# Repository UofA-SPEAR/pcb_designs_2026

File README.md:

# pcb_designs_2026
Repository for SPEAR 2026 PCB designs. KiCad is used as the PCB design software.
## Setup Instructions
Before opening any KiCad projects in this repository, the SPEAR_PCB_2026_DIR environment variable must be set as follows:

1. In the top toolbar, click "Preferences" then click "Configure Paths..." in the dropdown menu that appears as shown in figure 1.

**Figure 1**: Configuring KiCad file paths.

2. In the window that shows up, press the "+" button at the bottom left as shown in figure 2. This adds a new empty environment variable at the bottom of the environment variables list.

**Figure 2**: Adding a new environment variable.

3. Edit the name of the environment variable to be "SPEAR_PCB_2026_DIR" and edit the path to be the pcb_designs_2026 git repository. Setting the path can be done by clicking the folder button to the right of the path entry box with the entry box selected. The end result must look like figure 3.

**Figure 3**: Creating the SPEAR_PCB_2026_DIR environment variable.

4. Next, press "OK" to finalize the changes. Now your KiCad is ready to open projects in the repository.

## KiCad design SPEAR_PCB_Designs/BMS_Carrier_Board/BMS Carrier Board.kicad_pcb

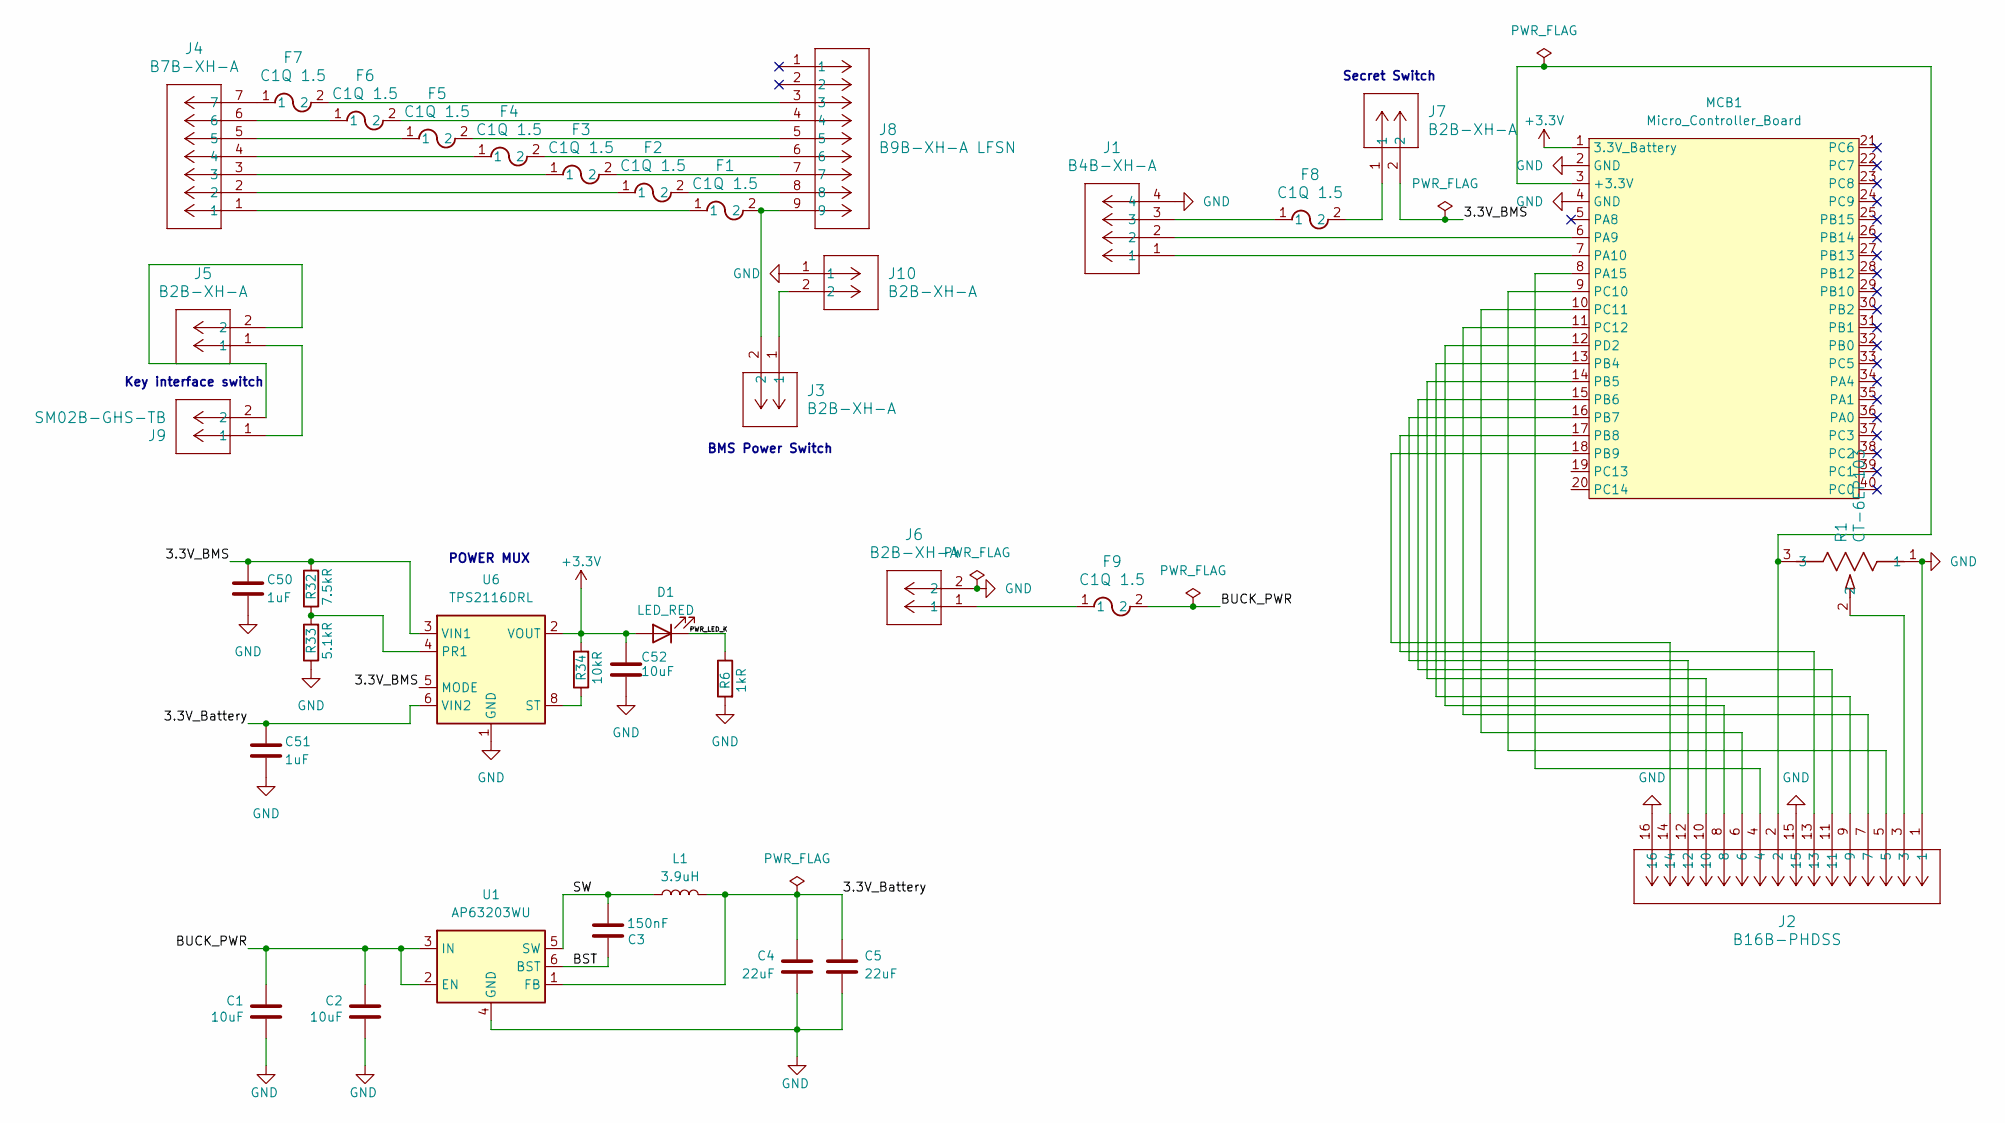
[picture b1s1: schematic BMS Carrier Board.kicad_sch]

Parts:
C1, C2: 10uF; CAPC3225X270N; DigiKey_Part_Number 490-14536-1-ND
C3: 150nF; CAP_CC1206_YAG; DigiKey_Part_Number 13-CC1206KRX7R8BB154CT-ND
C4, C5: 22uF; CAP_C3225X7R1C226M250AC; DigiKey_Part_Number 445-3955-1-ND
C50, C51: 1uF; C_0402_1005Metric; DigiKey_Part_Number 1276-1067-1-ND
C52: 10uF; C_0603_1608Metric; DigiKey_Part_Number 1276-1192-1-ND
D1: LED_RED; LED_0603_1608Metric; DigiKey_Part_Number 732-12015-1-ND
F1, F2, F3, F4, F5, F6, F7, F8, F9: C1Q 1.5; C1_BEL; DigiKey_Part_Number 5923-C1Q1.5CT-ND
J1: B4B-XH-A; CONN_B4B-XH-A_JST; DigiKey_Part_Number 455-B4B-XH-A-ND
J2: B16B-PHDSS; CONN16_B16B-PHDSS_JST
J3, J5, J6, J7: B2B-XH-A; CONN_B2B-XH-A_JST; DigiKey_Part_Number 455-B2B-XH-A-ND
J4: B7B-XH-A; CONN_B7B-XH-A_JST; DigiKey_Part_Number 455-B7B-XH-A-ND
J8: B9B-XH-A LFSN; CONN_B9B-XH-A_JST; DigiKey_Part_Number 455-B9B-XH-A-ND
J9: SM02B-GHS-TB; CONN_SM02B-GHS_JST; DigiKey_Part_Number 455-1564-1-ND
J10: B2B-XH-A; CONN_B2B-XH-A_JST
L1: 3.9uH; L_Wurth_WE-LHMI-1040_L1; DigiKey_Part_Number 732-74437368039CT-ND
MCB1: Micro_Controller_Board
R1: CT-6EP103; POT_CT-6EP103_NDC
R6: 1kR; R_0402_1005Metric; DigiKey_Part_Number 311-1.0KJRCT-ND
R32: 7.5kR; R_0402_1005Metric; DigiKey_Part_Number 311-7.50KLRCT-ND
R33: 5.1kR; R_0402_1005Metric; DigiKey_Part_Number 311-5.10KLRCT-ND
R34: 10kR; R_0402_1005Metric; DigiKey_Part_Number 311-10KJRCT-ND
U1: AP63203WU; TSOT-23-6; DigiKey_Part_Number AP63203WU-7DICT-ND
U6: TPS2116DRL; SOT-583-8; DigiKey_Part_Number 296-TPS2116DRLRCT-ND

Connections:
+3.3V: C52.1, D1.2 (A), MCB1.1 (3.3V_Battery), R34.2, U6.2 (VOUT), U6.7 (VOUT)
/3.3V_BMS: C50.1, J7.2, R32.2, U6.3 (VIN1), U6.5 (MODE)
/3.3V_Battery: C4.1, C5.1, C51.1, L1.2, U1.1 (FB), U6.6 (VIN2)
/BST: C3.2, U1.6 (BST)
/BUCK_PWR: C1.1, C2.1, F9.2, U1.2 (EN), U1.3 (IN)
/PWR_LED_K: D1.1 (K), R6.1
/SW: C3.1, L1.1, U1.5 (SW)
GND: C1.2, C2.2, C4.2, C5.2, C50.2, C51.2, C52.2, J1.4, J2.1, J2.15, J2.16, J6.2, J10.1, MCB1.2 (GND), MCB1.4 (GND), R1.1, R6.2, R33.1, U1.4 (GND), U6.1 (GND)
unnamed: F1.1, J4.1
unnamed: F1.2, J3.2, J8.9
unnamed: F2.1, J4.2
unnamed: F2.2, J8.8
unnamed: F3.1, J4.3
unnamed: F3.2, J8.7
unnamed: F4.1, J4.4
unnamed: F4.2, J8.6
unnamed: F5.1, J4.5
unnamed: F5.2, J8.5
unnamed: F6.1, J4.6
unnamed: F6.2, J8.4
unnamed: F7.1, J4.7
unnamed: F7.2, J8.3
unnamed: F8.1, J1.3
unnamed: F8.2, J7.1
unnamed: F9.1, J6.1
unnamed: J2.3, R1.2
unnamed: J5.1, J9.1
unnamed: J5.2, J9.2
unnamed: J3.1, J10.2
unnamed: J2.2, MCB1.3 (+3.3V), R1.3
unnamed: J1.2, MCB1.6 (PA9)
unnamed: J1.1, MCB1.7 (PA10)
unnamed: J2.4, MCB1.8 (PA15)
unnamed: J2.9, MCB1.13 (PB4)
unnamed: J2.10, MCB1.14 (PB5)
unnamed: J2.11, MCB1.15 (PB6)
unnamed: J2.12, MCB1.16 (PB7)
unnamed: J2.13, MCB1.17 (PB8)
unnamed: J2.14, MCB1.18 (PB9)
unnamed: J2.5, MCB1.9 (PC10)
unnamed: J2.6, MCB1.10 (PC11)
unnamed: J2.7, MCB1.11 (PC12)
unnamed: J2.8, MCB1.12 (PD2)
unnamed: R32.1, R33.2, U6.4 (PR1)
unnamed: R34.1, U6.8 (ST)

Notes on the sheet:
Key interface switch
POWER MUX
BMS Power Switch
Secret Switch

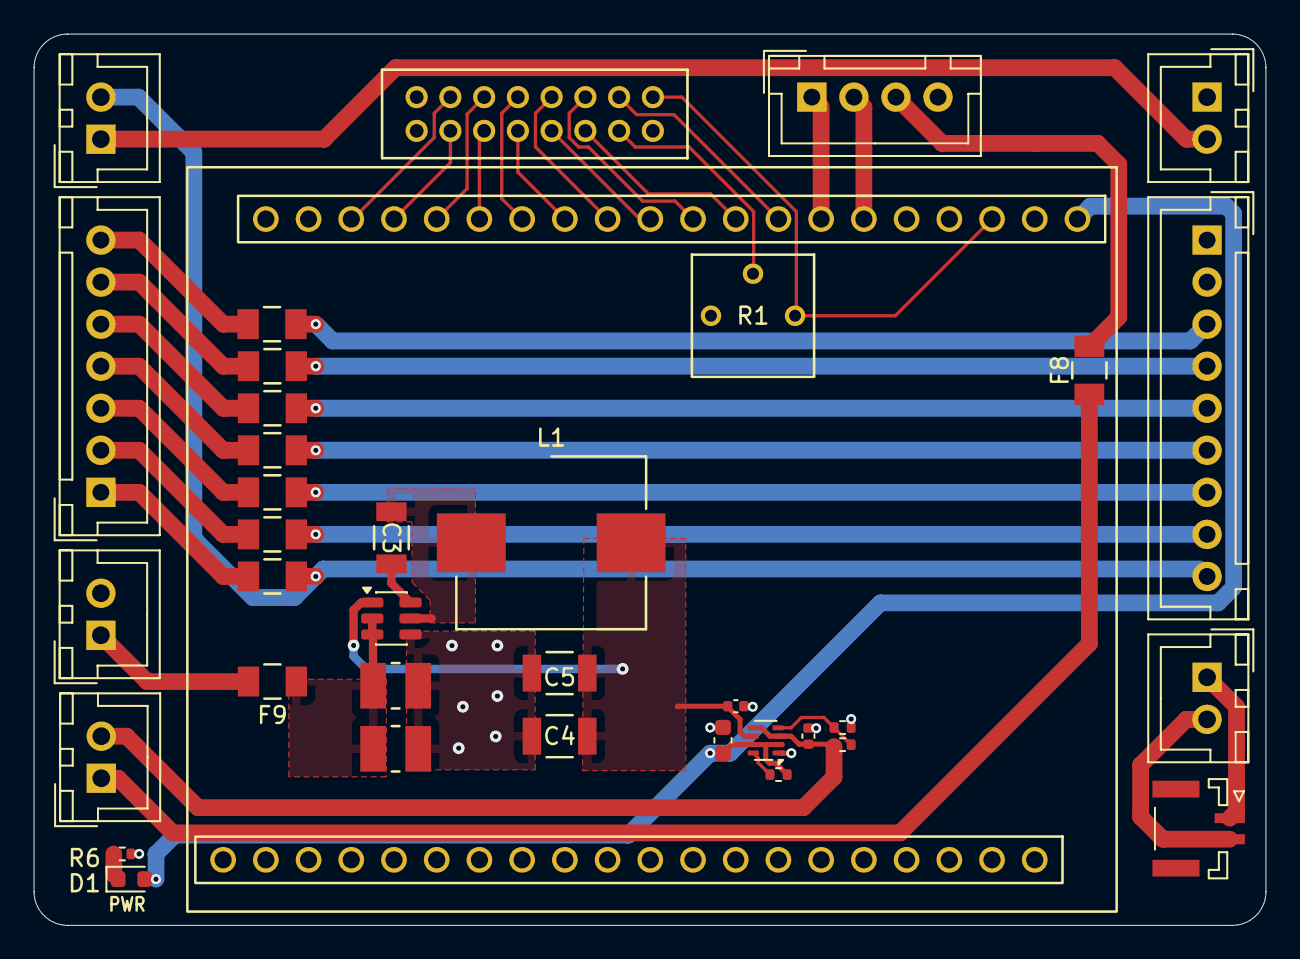
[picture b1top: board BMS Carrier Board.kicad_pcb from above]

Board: 2 copper layers, 73.2 x 53.0 mm, 37 parts (0 on the bottom side), 45 nets.

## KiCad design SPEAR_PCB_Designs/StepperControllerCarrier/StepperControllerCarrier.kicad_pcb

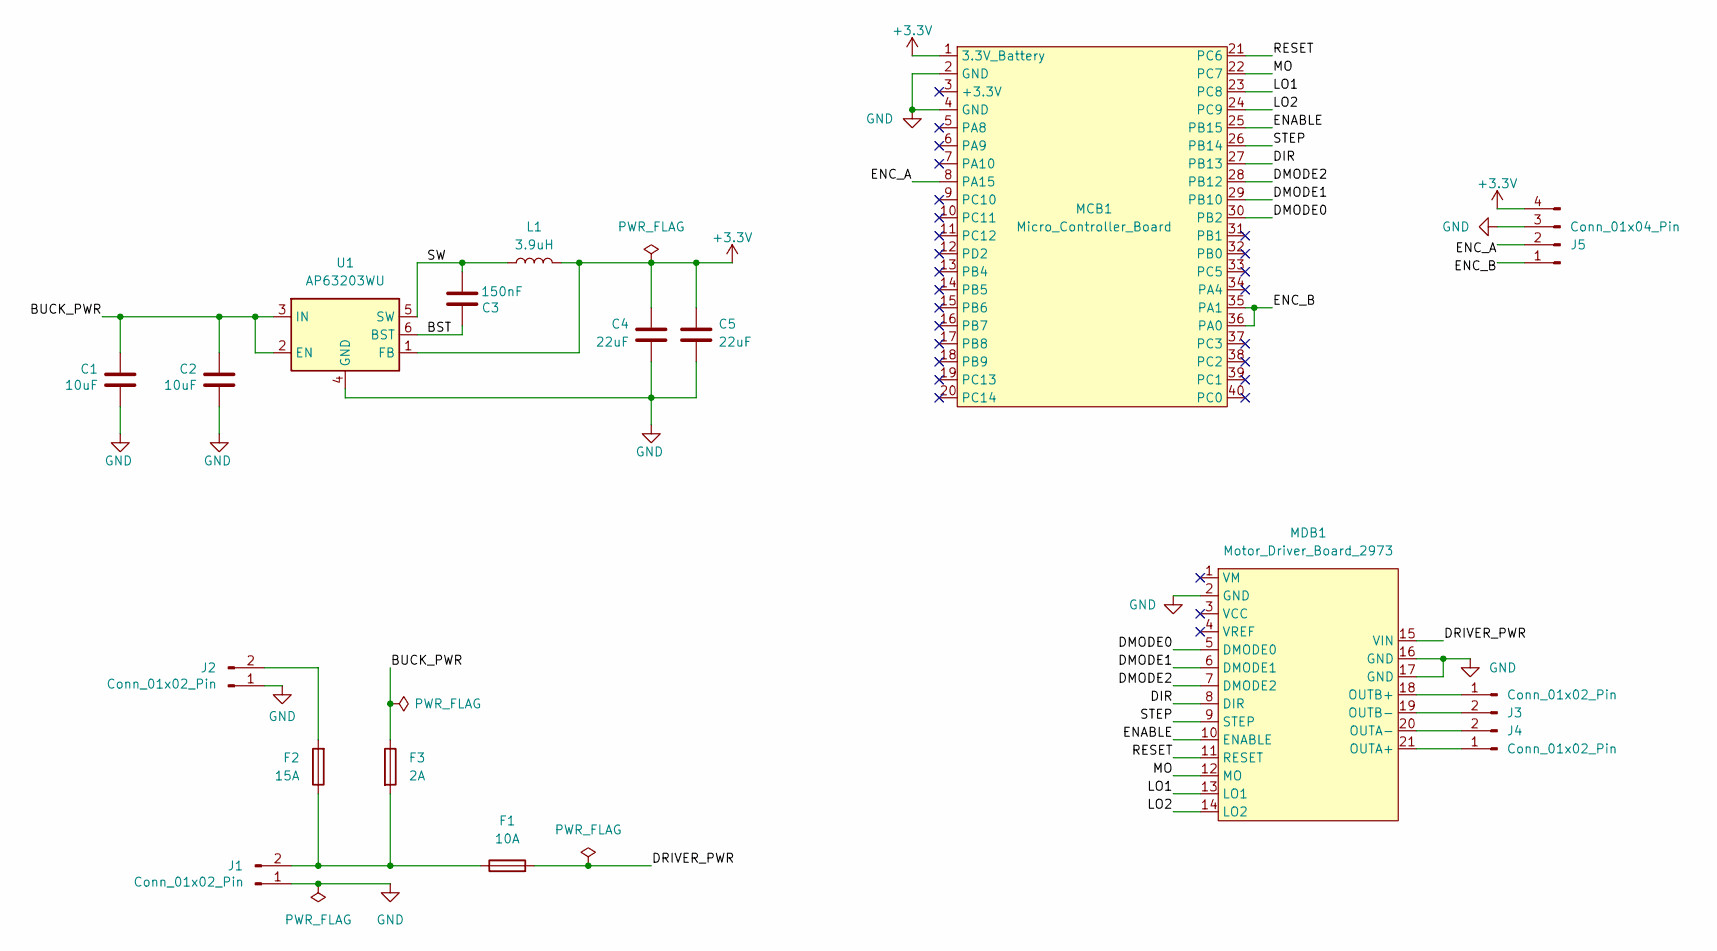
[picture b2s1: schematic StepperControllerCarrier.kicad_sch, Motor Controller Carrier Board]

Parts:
C1, C2: 10uF; CAPC3225X270N; DigiKey_Part_Number 490-14536-1-ND
C3: 150nF; CAP_CC1206_YAG; DigiKey_Part_Number 13-CC1206KRX7R8BB154CT-ND
C4, C5: 22uF; CAP_C3225X7R1C226M250AC; DigiKey_Part_Number 445-3955-1-ND
F1: 10A; FUSE_3557-10; PARTREV D; DigiKey_Part_Number 36-3557-10-ND
F2: 15A; FUSE_3557-15; PARTREV D; DigiKey_Part_Number 36-3557-15-ND
F3: 2A; FUS_LITTELFUSE_392_LTF; DigiKey_Part_Number F5502CT-ND
J1, J2, J3, J4: Conn_01x02_Pin; AMASS_XT30PW-M_1x02_P2.50mm_Horizontal_1
J5: Conn_01x04_Pin; JST_XH_S4B-XH-A-1_1x04_P2.50mm_Horizontal; DigiKey_Part_Number 455-S4B-XH-A-1-ND
L1: 3.9uH; L_Wurth_WE-LHMI-1040_L1; DigiKey_Part_Number 732-74437368039CT-ND
MCB1: Micro_Controller_Board
MDB1: Motor_Driver_Board_2973
U1: AP63203WU; TSOT-23-6; DigiKey_Part_Number AP63203WU-7DICT-ND

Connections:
+3.3V: C4.1, C5.1, J5.4, L1.2, MCB1.1 (3.3V_Battery), U1.1 (FB)
/BST: C3.2, U1.6 (BST)
/BUCK_PWR: C1.1, C2.1, F3.1, U1.2 (EN), U1.3 (IN)
/DIR: MCB1.27 (PB13), MDB1.8 (DIR)
/DMODE0: MCB1.30 (PB2), MDB1.5 (DMODE0)
/DMODE1: MCB1.29 (PB10), MDB1.6 (DMODE1)
/DMODE2: MCB1.28 (PB12), MDB1.7 (DMODE2)
/DRIVER_PWR: F1.2_1, F1.2_2, MDB1.15 (VIN)
/ENABLE: MCB1.25 (PB15), MDB1.10 (ENABLE)
/ENC_A: J5.2, MCB1.8 (PA15)
/ENC_B: J5.1, MCB1.35 (PA1), MCB1.36 (PA0)
/LO1: MCB1.23 (PC8), MDB1.13 (LO1)
/LO2: MCB1.24 (PC9), MDB1.14 (LO2)
/MO: MCB1.22 (PC7), MDB1.12 (MO)
/RESET: MCB1.21 (PC6), MDB1.11 (RESET)
/STEP: MCB1.26 (PB14), MDB1.9 (STEP)
/SW: C3.1, L1.1, U1.5 (SW)
GND: C1.2, C2.2, C4.2, C5.2, J1.1, J2.1, J5.3, MCB1.2 (GND), MCB1.4 (GND), MDB1.2 (GND), MDB1.16 (GND), MDB1.17 (GND), U1.4 (GND)
unnamed: F1.1_1, F1.1_2, F2.1_1, F2.1_2, F3.2, J1.2
unnamed: F2.2_1, F2.2_2, J2.2
unnamed: J3.1, MDB1.18 (OUTB+)
unnamed: J3.2, MDB1.19 (OUTB-)
unnamed: J4.1, MDB1.21 (OUTA+)
unnamed: J4.2, MDB1.20 (OUTA-)

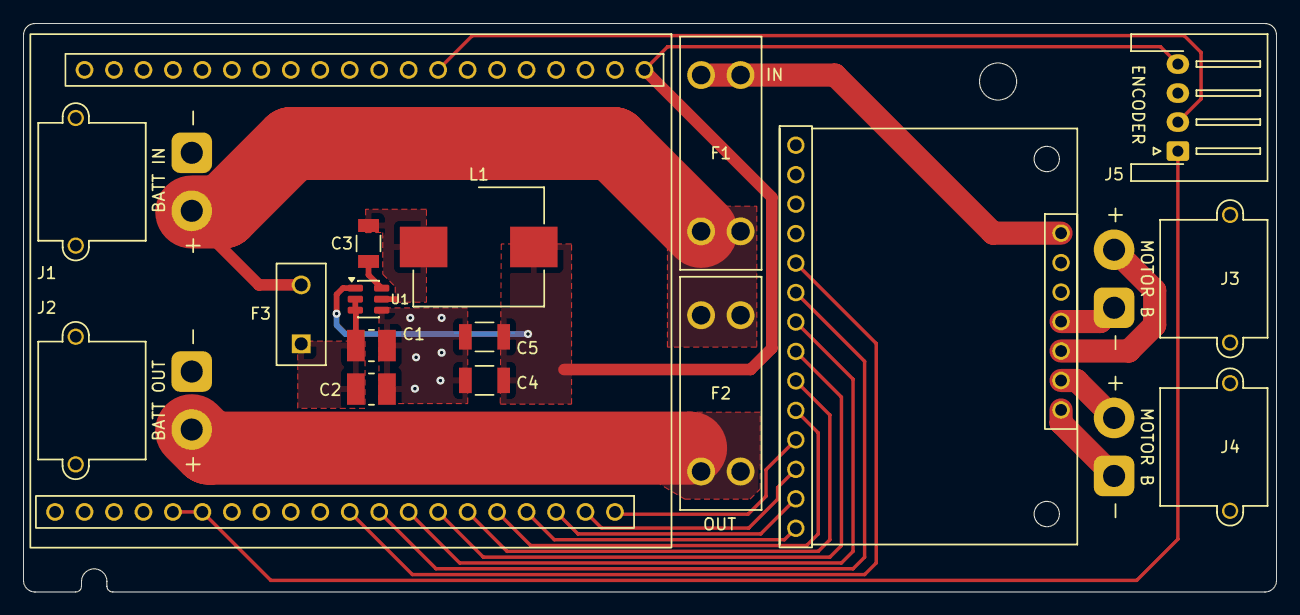
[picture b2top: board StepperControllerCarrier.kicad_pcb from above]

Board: 2 copper layers, 108.0 x 49.0 mm, 17 parts (0 on the bottom side), 24 nets.

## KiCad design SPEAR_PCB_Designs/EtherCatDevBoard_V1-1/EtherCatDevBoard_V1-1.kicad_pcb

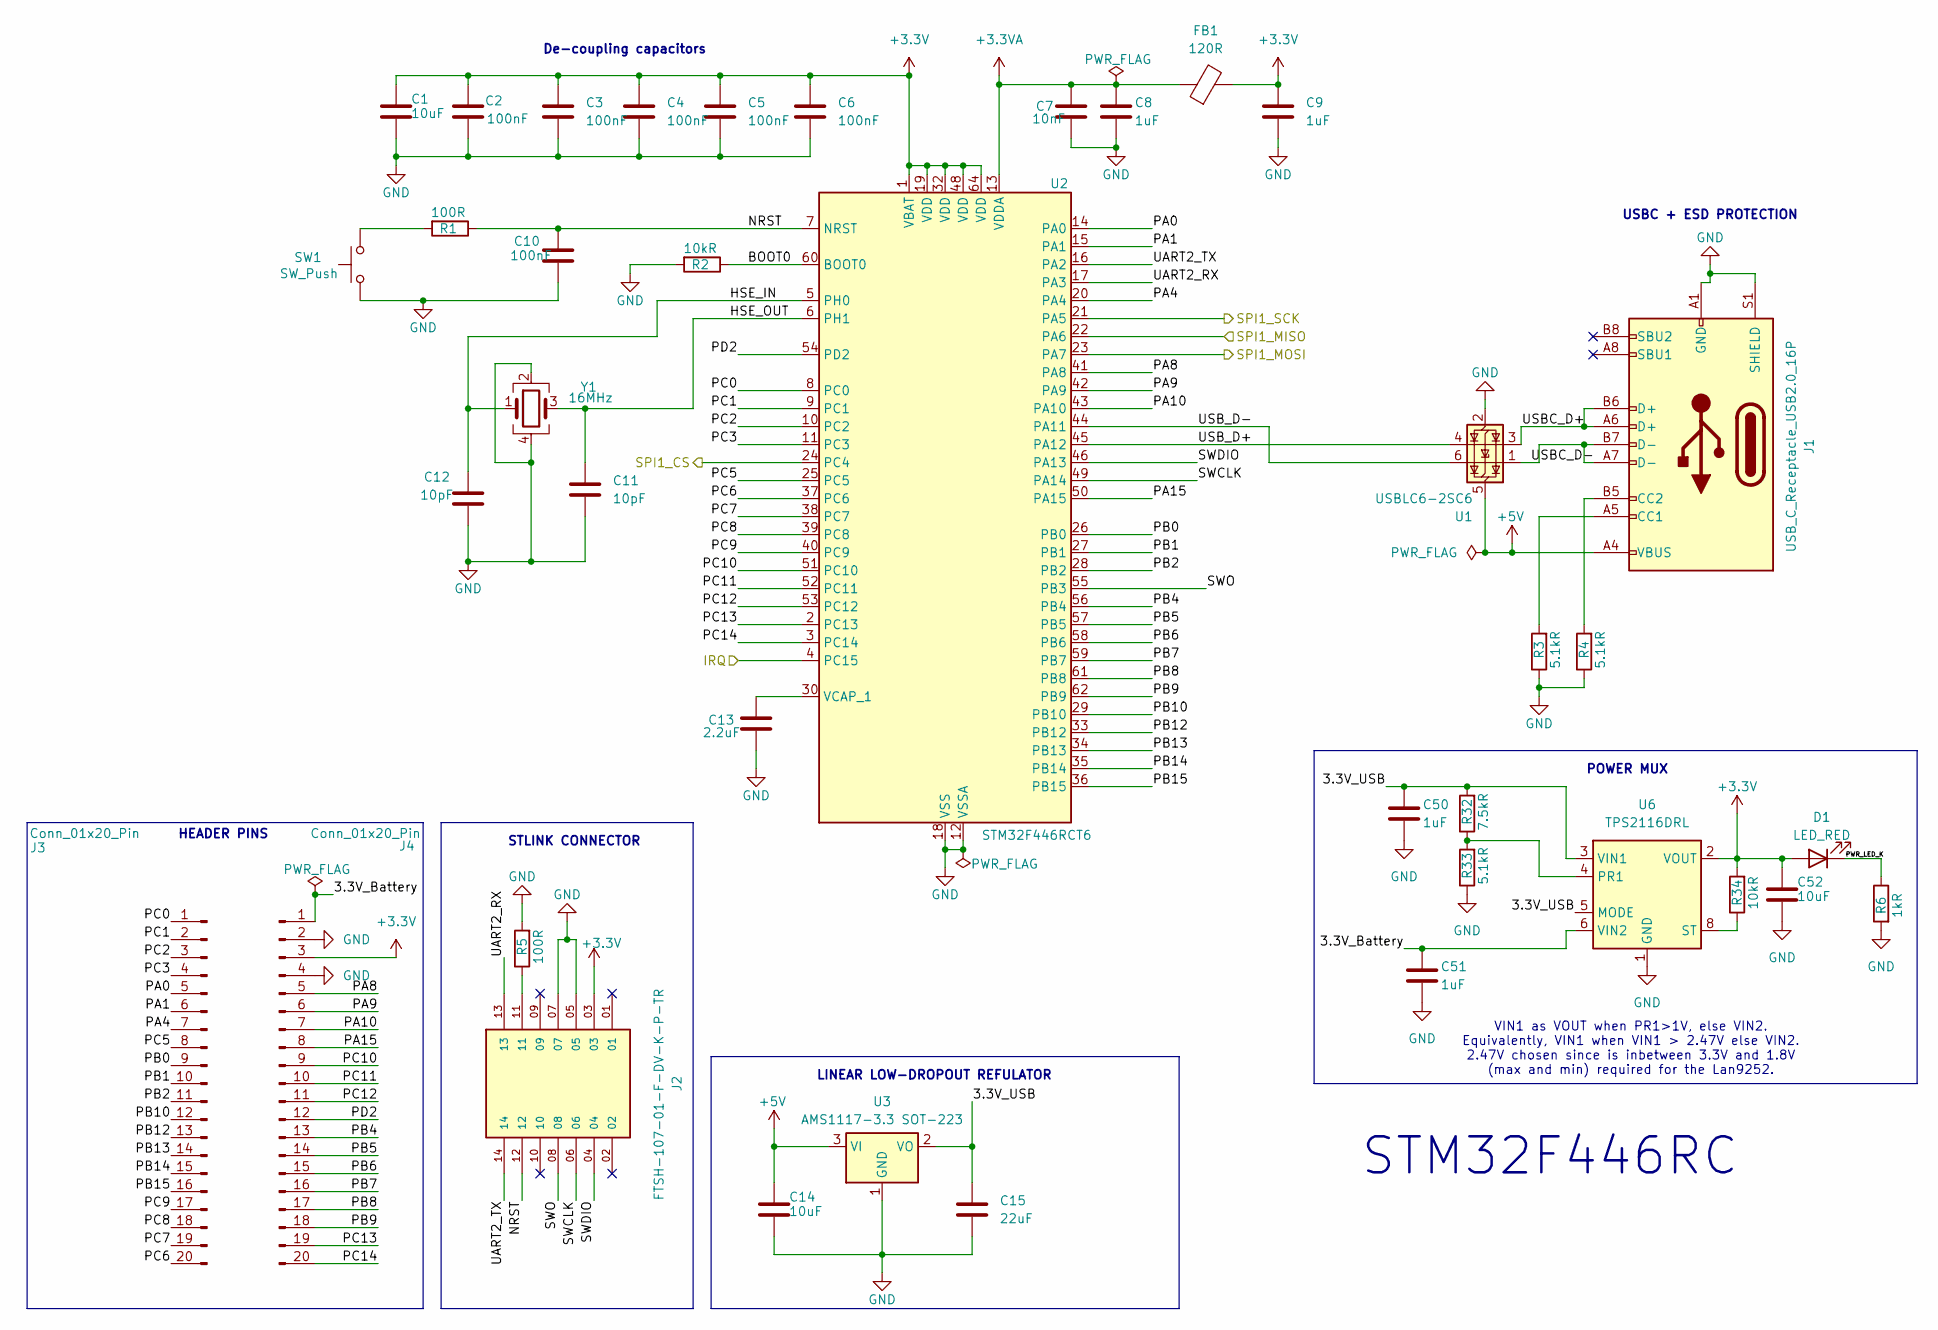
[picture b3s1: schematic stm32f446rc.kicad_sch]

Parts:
C1, C14, C52: 10uF; C_0603_1608Metric; DigiKey_Part_Number 1276-1192-1-ND
C2, C3, C4, C5, C6, C10: 100nF; C_0402_1005Metric; DigiKey_Part_Number 1276-1043-1-ND
C7: 10nF; C_0402_1005Metric; DigiKey_Part_Number 1276-1051-1-ND
C8, C9, C50, C51: 1uF; C_0402_1005Metric; DigiKey_Part_Number 1276-1067-1-ND
C11, C12: 10pF; C_0402_1005Metric; DigiKey_Part_Number 1276-1139-1-ND
C13: 2.2uF; C_0402_1005Metric; DigiKey_Part_Number 1276-1108-1-ND
C15: 22uF; C_0805_2012Metric; DigiKey_Part_Number 1276-CL21A226MAYNNNECT-ND
D1: LED_RED; LED_0603_1608Metric; DigiKey_Part_Number 732-12015-1-ND
FB1: 120R; L_0603_1608Metric; DigiKey_Part_Number 490-5254-1-ND
J1: USB_C_Receptacle_USB2.0_16P; USB_C_Receptacle_GCT_USB4105-xx-A_16P_TopMnt_Horizontal; DigiKey_Part_Number 2073-USB4105-GF-A-120CT-ND
J2: FTSH-107-01-F-DV-K-P-TR; SAMTEC_FTSH-107-01-F-DV-K-P-TR; PARTREV R; DigiKey_Part_Number SAM13170CT-ND
J3, J4: Conn_01x20_Pin; PinHeader_1x20_P2.54mm_Vertical; DigiKey_Part_Number 2057-PH1-20-UA-ND
R1, R5: 100R; R_0402_1005Metric; DigiKey_Part_Number 311-100LRCT-ND
R2, R34: 10kR; R_0402_1005Metric; DigiKey_Part_Number 311-10KJRCT-ND
R3, R4, R33: 5.1kR; R_0402_1005Metric; DigiKey_Part_Number 311-5.10KLRCT-ND
R6: 1kR; R_0402_1005Metric; DigiKey_Part_Number 311-1.0KJRCT-ND
R32: 7.5kR; R_0402_1005Metric; DigiKey_Part_Number 311-7.50KLRCT-ND
SW1: SW_Push; SW_Tactile_SPST_NO_Straight_CK_PTS636Sx25SMTRLFS; DigiKey_Part_Number CKN12322-1-ND
U1: USBLC6-2SC6; SOT-23-6; DigiKey_Part_Number 497-5235-1-ND
U2: STM32F446RCT6; LQFP-64_10x10mm_P0.5mm; DigiKey_Part_Number 497-17472-ND
U3: AMS1117-3.3 SOT-223; SOT-223-3_TabPin2; DigiKey_Part_Number 5399-AMS1117-3.3SOT-223CT-ND
U6: TPS2116DRL; SOT-583-8; DigiKey_Part_Number 296-TPS2116DRLRCT-ND
Y1: 16MHz; Crystal_SMD_2520-4Pin_2.5x2.0mm; DigiKey_Part_Number 2151-R2520-16.000-10-1020-EXT-TRCT-ND

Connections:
+3.3V: C1.1, C2.1, C3.1, C4.1, C5.1, C6.1, C9.1, C52.1, D1.2 (A), FB1.2, J2.03, J4.3, R34.2, U2.1 (VBAT), U2.19 (VDD), U2.32 (VDD), U2.48 (VDD), U2.64 (VDD), U6.2 (VOUT), U6.7 (VOUT); also elsewhere on the board
+3.3VA: C7.1, C8.1, FB1.1, U2.13 (VDDA)
+5V: C14.1, J1.A4 (VBUS), J1.A9 (VBUS), J1.B4 (VBUS), J1.B9 (VBUS), U1.5 (VBUS), U3.3 (VI)
/LAN9252/IRQ: U2.4 (PC15); also elsewhere on the board
/LAN9252/MISO: U2.22 (PA6); also elsewhere on the board
/LAN9252/MOSI: U2.23 (PA7); also elsewhere on the board
/LAN9252/SCK: U2.21 (PA5); also elsewhere on the board
/LAN9252/SCS: U2.24 (PC4); also elsewhere on the board
/STM32F446RC/3.3V_Battery: C51.1, J4.1, U6.6 (VIN2)
/STM32F446RC/3.3V_USB: C15.1, C50.1, R32.2, U3.2 (VO), U6.3 (VIN1), U6.5 (MODE)
/STM32F446RC/BOOT0: R2.1, U2.60 (BOOT0)
/STM32F446RC/HSE_IN: C12.1, U2.5 (PH0), Y1.1
/STM32F446RC/HSE_OUT: C11.1, U2.6 (PH1), Y1.3
/STM32F446RC/NRST: C10.1, J2.12, R1.1, U2.7 (NRST)
/STM32F446RC/PA0: J3.5, U2.14 (PA0)
/STM32F446RC/PA1: J3.6, U2.15 (PA1)
/STM32F446RC/PA4: J3.7, U2.20 (PA4)
/STM32F446RC/PA8: J4.5, U2.41 (PA8)
/STM32F446RC/PA9: J4.6, U2.42 (PA9)
/STM32F446RC/PA10: J4.7, U2.43 (PA10)
/STM32F446RC/PA15: J4.8, U2.50 (PA15)
/STM32F446RC/PB0: J3.9, U2.26 (PB0)
/STM32F446RC/PB1: J3.10, U2.27 (PB1)
/STM32F446RC/PB2: J3.11, U2.28 (PB2)
/STM32F446RC/PB4: J4.13, U2.56 (PB4)
/STM32F446RC/PB5: J4.14, U2.57 (PB5)
/STM32F446RC/PB6: J4.15, U2.58 (PB6)
/STM32F446RC/PB7: J4.16, U2.59 (PB7)
/STM32F446RC/PB8: J4.17, U2.61 (PB8)
/STM32F446RC/PB9: J4.18, U2.62 (PB9)
/STM32F446RC/PB10: J3.12, U2.29 (PB10)
/STM32F446RC/PB12: J3.13, U2.33 (PB12)
/STM32F446RC/PB13: J3.14, U2.34 (PB13)
/STM32F446RC/PB14: J3.15, U2.35 (PB14)
/STM32F446RC/PB15: J3.16, U2.36 (PB15)
/STM32F446RC/PC0: J3.1, U2.8 (PC0)
/STM32F446RC/PC1: J3.2, U2.9 (PC1)
/STM32F446RC/PC2: J3.3, U2.10 (PC2)
/STM32F446RC/PC3: J3.4, U2.11 (PC3)
/STM32F446RC/PC5: J3.8, U2.25 (PC5)
/STM32F446RC/PC6: J3.20, U2.37 (PC6)
/STM32F446RC/PC7: J3.19, U2.38 (PC7)
/STM32F446RC/PC8: J3.18, U2.39 (PC8)
/STM32F446RC/PC9: J3.17, U2.40 (PC9)
/STM32F446RC/PC10: J4.9, U2.51 (PC10)
/STM32F446RC/PC11: J4.10, U2.52 (PC11)
/STM32F446RC/PC12: J4.11, U2.53 (PC12)
/STM32F446RC/PC13: J4.19, U2.2 (PC13)
/STM32F446RC/PC14: J4.20, U2.3 (PC14)
/STM32F446RC/PD2: J4.12, U2.54 (PD2)
/STM32F446RC/PWR_LED_K: D1.1 (K), R6.1
/STM32F446RC/SWCLK: J2.06, U2.49 (PA14)
/STM32F446RC/SWDIO: J2.04, U2.46 (PA13)
/STM32F446RC/SWO: J2.08, U2.55 (PB3)
/STM32F446RC/UART2_RX: J2.13, U2.17 (PA3)
/STM32F446RC/UART2_TX: J2.14, U2.16 (PA2)
/STM32F446RC/USBC_D+: J1.A6 (D+), J1.B6 (D+), U1.3 (I/O2)
/STM32F446RC/USBC_D-: J1.A7 (D-), J1.B7 (D-), U1.1 (I/O1)
/STM32F446RC/USB_D+: U1.4 (I/O2), U2.45 (PA12)
/STM32F446RC/USB_D-: U1.6 (I/O1), U2.44 (PA11)
GND: C1.2, C2.2, C3.2, C4.2, C5.2, C6.2, C7.2, C8.2, C9.2, C10.2, C11.2, C12.2, C13.2, C14.2, C15.2, C50.2, C51.2, C52.2, J1.A1 (GND), J1.A12 (GND), J1.B1 (GND), J1.B12 (GND), J1.S1 (SHIELD), J2.05, J2.07, J4.2, J4.4, R2.2, R3.1, R4.1, R5.2, R6.2, R33.1, SW1.1, U1.2 (GND), U2.12 (VSSA), U2.18 (VSS), U2.31 (VSS), U2.47 (VSS), U2.63 (VSS), U3.1 (GND), U6.1 (GND), Y1.2, Y1.4; also elsewhere on the board
unnamed: J1.A5 (CC1), R3.2
unnamed: J1.B5 (CC2), R4.2
unnamed: J2.11, R5.1
unnamed: R1.2, SW1.2
unnamed: C13.1, U2.30 (VCAP_1)
unnamed: R32.1, R33.2, U6.4 (PR1)
unnamed: R34.1, U6.8 (ST)

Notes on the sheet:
POWER MUX
STLINK CONNECTOR
VIN1 as VOUT when PR1>1V, else VIN2. Equivalently, VIN1 when VIN1 > 2.47V else VIN2. 2.47V chosen since is inbetween 3.3V and 1.8V (max and min) required for the Lan9252.
De-coupling capacitors
LINEAR LOW-DROPOUT REFULATOR
STM32F446RC
USBC + ESD PROTECTION
HEADER PINS

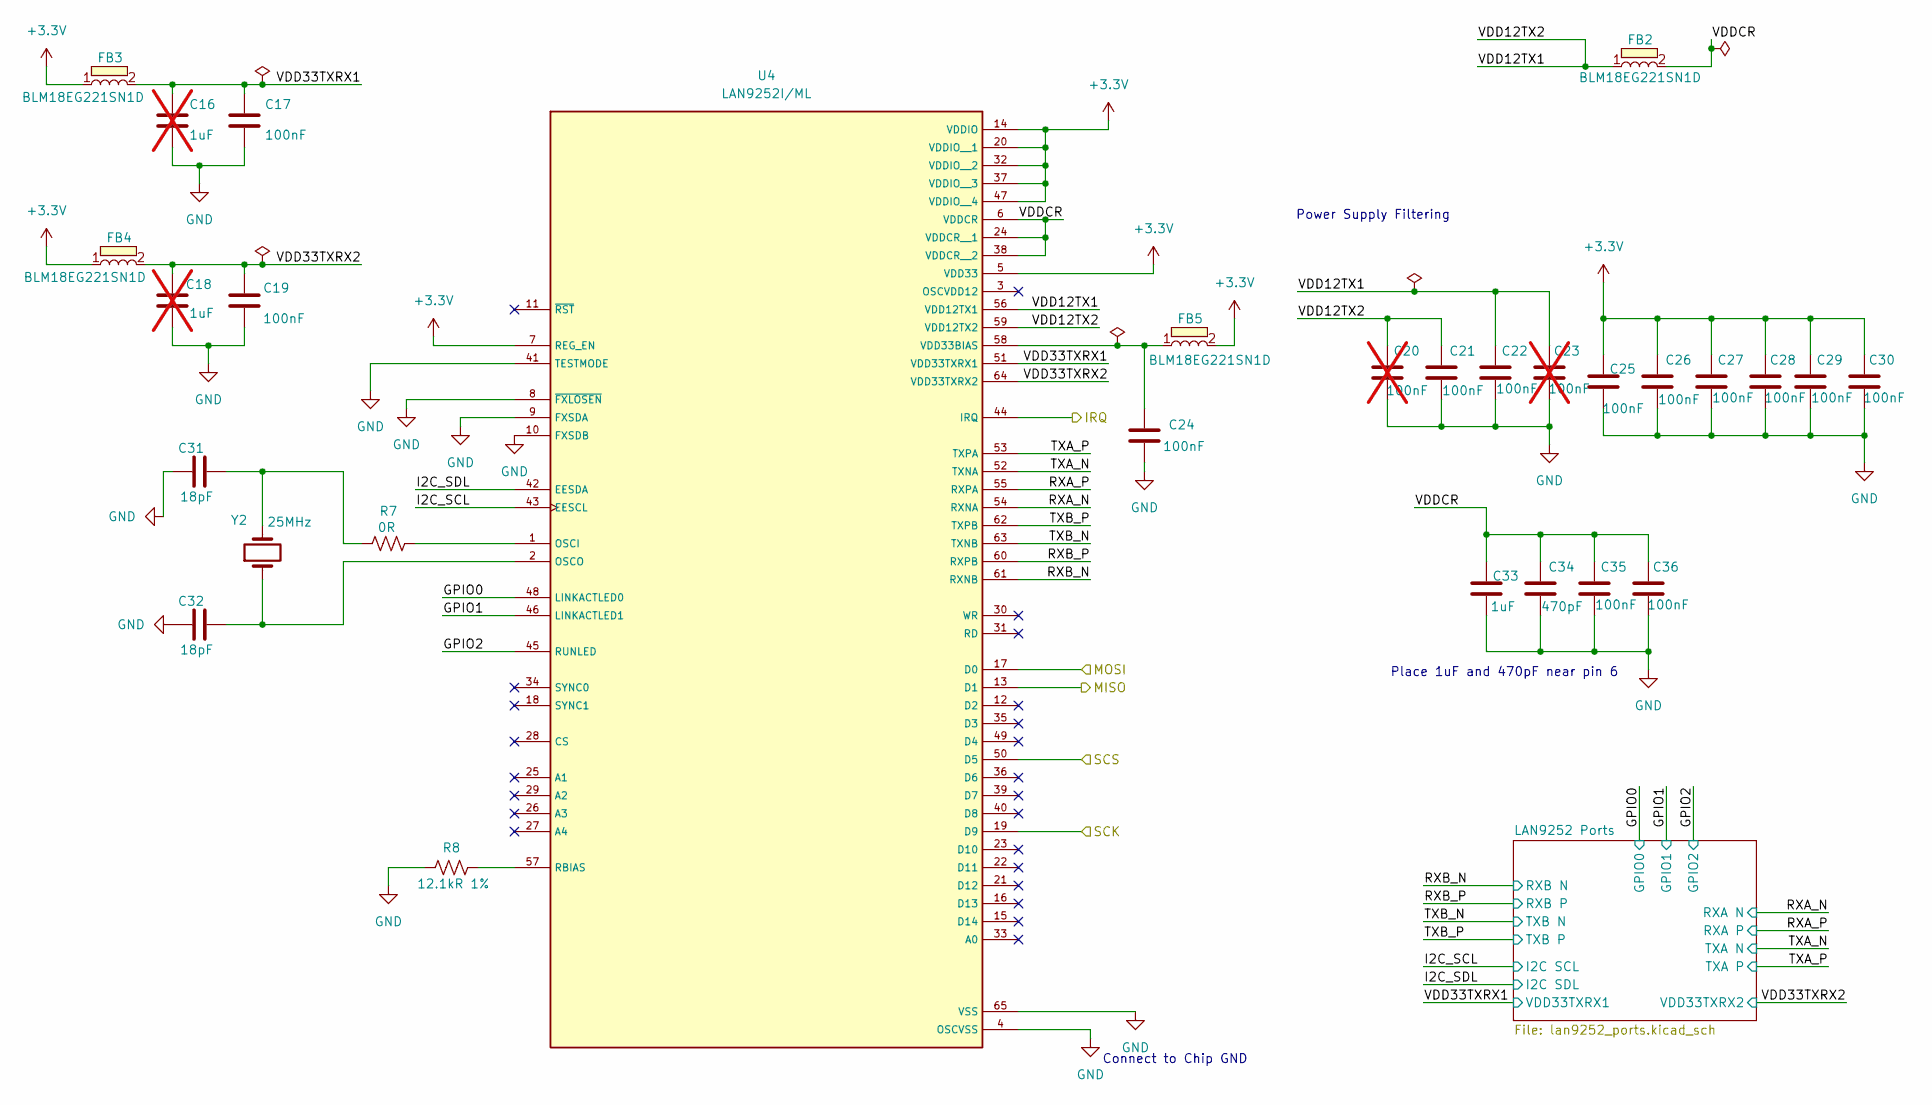
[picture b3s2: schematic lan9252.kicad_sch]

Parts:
C16, C18: 1uF; C_0402_1005Metric; DigiKey_Part_Number 1276-1067-1-ND; not fitted
C17, C19, C21, C22, C24, C25, C26, C27, C28, C29, C30, C35, C36: 100nF; C_0402_1005Metric; DigiKey_Part_Number 1276-1043-1-ND
C20, C23: 100nF; C_0402_1005Metric; DigiKey_Part_Number 1276-1043-1-ND; not fitted
C31, C32: 18pF; C_0402_1005Metric; DigiKey_Part_Number 1276-6612-1-ND
C33: 1uF; C_0402_1005Metric; DigiKey_Part_Number 1276-1067-1-ND
C34: 470pF; C_0402_1005Metric; DigiKey_Part_Number 1276-1566-1-ND
FB2, FB3, FB4, FB5: BLM18EG221SN1D; Ferrite_bead; DigiKey_Part_Number 490-3992-1-ND
R7: 0R; R_0402_1005Metric; DigiKey_Part_Number 311-0.0JRCT-ND
R8: 12.1kR 1%; R_0402_1005Metric; DigiKey_Part_Number 311-12.1KLRCT-ND
U4: LAN9252I/ML; LAN9252_QFN UPDATED; DigiKey_Part_Number LAN9252I/ML-ND
Y2: 25MHz; Y_Wurth_WE-XTAL_Quartz-HC49-4HSMX; DigiKey_Part_Number 732-830056463CT-ND

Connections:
+3.3V: C25.1, C26.1, C27.1, C28.1, C29.1, C30.1, FB3.1, FB4.1, FB5.2, U4.5 (VDD33), U4.7 (REG_EN), U4.14 (VDDIO), U4.20 (VDDIO__1), U4.32 (VDDIO__2), U4.37 (VDDIO__3), U4.47 (VDDIO__4); also elsewhere on the board
/LAN9252/GPIO0: U4.48 (LINKACTLED0); also elsewhere on the board
/LAN9252/GPIO1: U4.46 (LINKACTLED1); also elsewhere on the board
/LAN9252/GPIO2: U4.45 (RUNLED); also elsewhere on the board
/LAN9252/I2C_SCL: U4.43 (EESCL); also elsewhere on the board
/LAN9252/I2C_SDL: U4.42 (EESDA); also elsewhere on the board
/LAN9252/IRQ: U4.44 (IRQ); also elsewhere on the board
/LAN9252/MISO: U4.13 (D1); also elsewhere on the board
/LAN9252/MOSI: U4.17 (D0); also elsewhere on the board
/LAN9252/RXA_N: U4.54 (RXNA); also elsewhere on the board
/LAN9252/RXA_P: U4.55 (RXPA); also elsewhere on the board
/LAN9252/RXB_N: U4.61 (RXNB); also elsewhere on the board
/LAN9252/RXB_P: U4.60 (RXPB); also elsewhere on the board
/LAN9252/SCK: U4.19 (D9); also elsewhere on the board
/LAN9252/SCS: U4.50 (D5); also elsewhere on the board
/LAN9252/TXA_N: U4.52 (TXNA); also elsewhere on the board
/LAN9252/TXA_P: U4.53 (TXPA); also elsewhere on the board
/LAN9252/TXB_N: U4.63 (TXNB); also elsewhere on the board
/LAN9252/TXB_P: U4.62 (TXPB); also elsewhere on the board
/LAN9252/VDD12TX1: C20.1, C21.1, C22.1, C23.1, FB2.1, U4.56 (VDD12TX1), U4.59 (VDD12TX2)
/LAN9252/VDD33TXRX1: C16.1, C17.1, FB3.2, U4.51 (VDD33TXRX1); also elsewhere on the board
/LAN9252/VDD33TXRX2: C18.1, C19.1, FB4.2, U4.64 (VDD33TXRX2); also elsewhere on the board
/LAN9252/VDDCR: C33.1, C34.1, C35.1, C36.1, FB2.2, U4.6 (VDDCR), U4.24 (VDDCR__1), U4.38 (VDDCR__2)
GND: C16.2, C17.2, C18.2, C19.2, C20.2, C21.2, C22.2, C23.2, C24.2, C25.2, C26.2, C27.2, C28.2, C29.2, C30.2, C31.1, C32.1, C33.2, C34.2, C35.2, C36.2, R8.1, U4.4 (OSCVSS), U4.8 (~FXLOSEN), U4.9 (FXSDA), U4.10 (FXSDB), U4.41 (TESTMODE), U4.65 (VSS); also elsewhere on the board
unnamed: C31.2, R7.1, Y2.2
unnamed: R7.2, U4.1 (OSCI)
unnamed: C32.2, U4.2 (OSCO), Y2.1
unnamed: R8.2, U4.57 (RBIAS)
unnamed: C24.1, FB5.1, U4.58 (VDD33BIAS)

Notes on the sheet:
Place 1uF and 470pF near pin 6
Connect to Chip GND
Power Supply Filtering
